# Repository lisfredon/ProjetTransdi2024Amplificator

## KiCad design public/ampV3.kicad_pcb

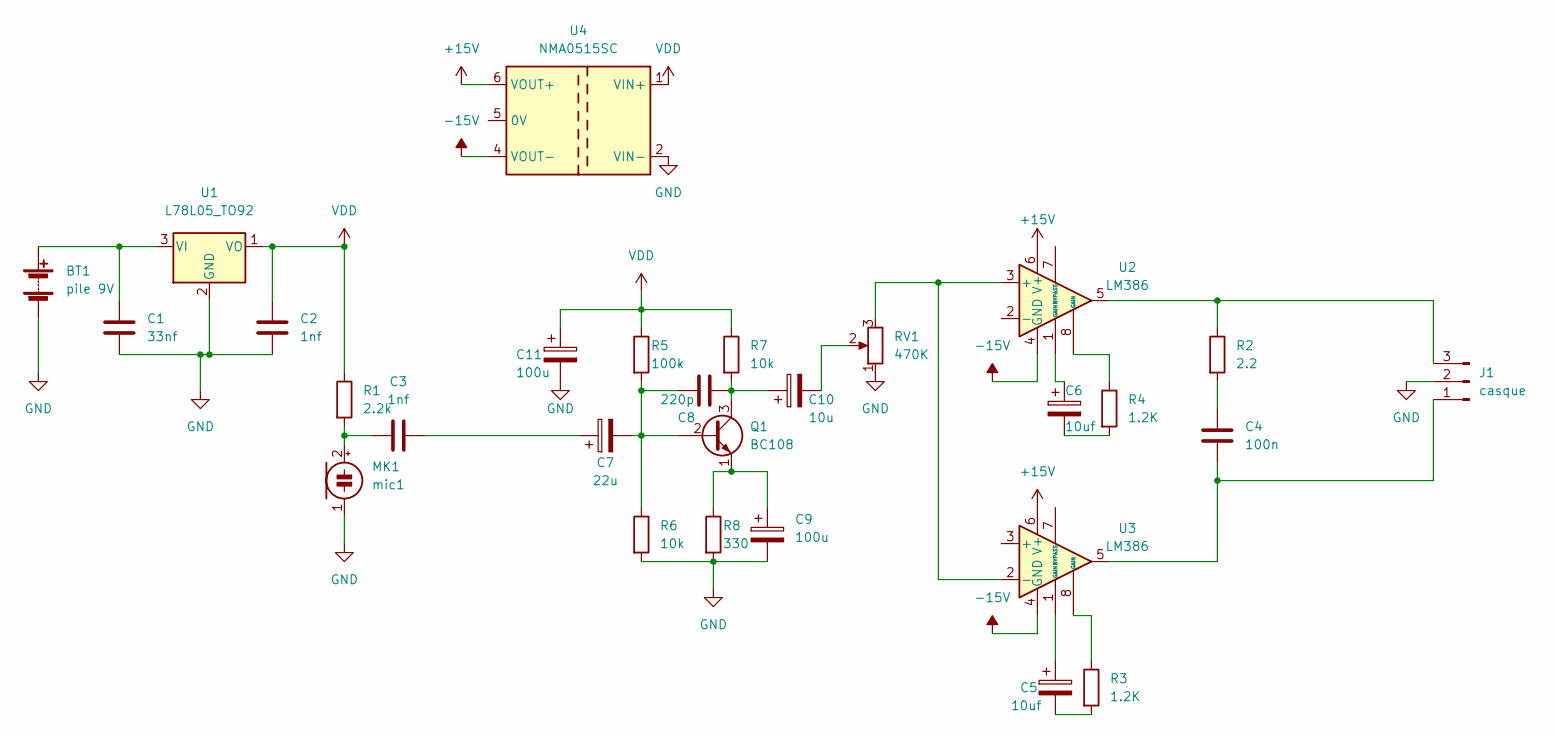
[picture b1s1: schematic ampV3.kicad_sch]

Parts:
BT1: pile 9V; PinHeader_1x02_P2.00mm_Vertical
C1: 33nf; C_Rect_L7.2mm_W3.0mm_P5.00mm_FKS2_FKP2_MKS2_MKP2
C2, C3: 1nf; C_Rect_L7.2mm_W3.0mm_P5.00mm_FKS2_FKP2_MKS2_MKP2
C4: 100n; C_Rect_L7.2mm_W3.0mm_P5.00mm_FKS2_FKP2_MKS2_MKP2
C5, C6: 10uf; CP_Radial_D6.3mm_P2.50mm
C7: 22u; CP_Radial_D6.3mm_P2.50mm
C8: 220p; C_Rect_L7.2mm_W2.5mm_P5.00mm_FKS2_FKP2_MKS2_MKP2
C9, C11: 100u; CP_Radial_D6.3mm_P2.50mm
C10: 10u; CP_Radial_D6.3mm_P2.50mm
J1: casque; PinHeader_1x03_P2.00mm_Vertical
MK1: mic1; PinHeader_1x02_P2.00mm_Vertical
Q1: BC108; TO-18-3
R1: 2.2k; R_Axial_DIN0204_L3.6mm_D1.6mm_P7.62mm_Horizontal
R2: 2.2; R_Axial_DIN0204_L3.6mm_D1.6mm_P7.62mm_Horizontal
R3, R4: 1.2K; R_Axial_DIN0204_L3.6mm_D1.6mm_P7.62mm_Horizontal
R5: 100k; R_Axial_DIN0204_L3.6mm_D1.6mm_P7.62mm_Horizontal
R6, R7: 10k; R_Axial_DIN0204_L3.6mm_D1.6mm_P7.62mm_Horizontal
R8: 330; R_Axial_DIN0204_L3.6mm_D1.6mm_P7.62mm_Horizontal
RV1: 470K; Potentiometer_Piher_PT-10-V05_Vertical
U1: L78L05_TO92; TO-92_Inline_Wide
U2, U3: LM386; DIP-8_W7.62mm_Socket
U4: NMA0515SC; Converter_DCDC_Murata_NMAxxxxSC_THT

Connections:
+15V: U2.6 (V+), U3.6 (V+), U4.6 (VOUT+)
-15V: U2.4 (GND), U3.4 (GND), U4.4 (VOUT-)
GND: BT1.2 (-), C1.2, C2.2, C9.2, C11.2, J1.2, MK1.1 (-), R6.2, R8.2, RV1.1, U1.2 (GND), U4.2 (VIN-)
unnamed: BT1.1 (+), C1.1, U1.3 (VI)
unnamed: C3.2, C7.1
unnamed: C4.1, R2.2
unnamed: C5.1, U3.1 (GAIN)
unnamed: C5.2, R3.2
unnamed: C6.1, U2.1 (GAIN)
unnamed: C6.2, R4.2
unnamed: C10.2, RV1.2
unnamed: C4.2, J1.1, U3.5
unnamed: J1.3, R2.1, U2.5
unnamed: C3.1, MK1.2 (+), R1.2
unnamed: C7.2, C8.1, Q1.2 (B), R5.2, R6.1
unnamed: C8.2, C10.1, Q1.3 (C), R7.2
unnamed: C9.1, Q1.1 (E), R8.1
unnamed: R3.1, U3.8 (GAIN)
unnamed: R4.1, U2.8 (GAIN)
unnamed: RV1.3, U2.3 (+), U3.2 (-)
VDD: C2.1, C11.1, R1.1, R5.1, R7.1, U1.1 (VO), U4.1 (VIN+)

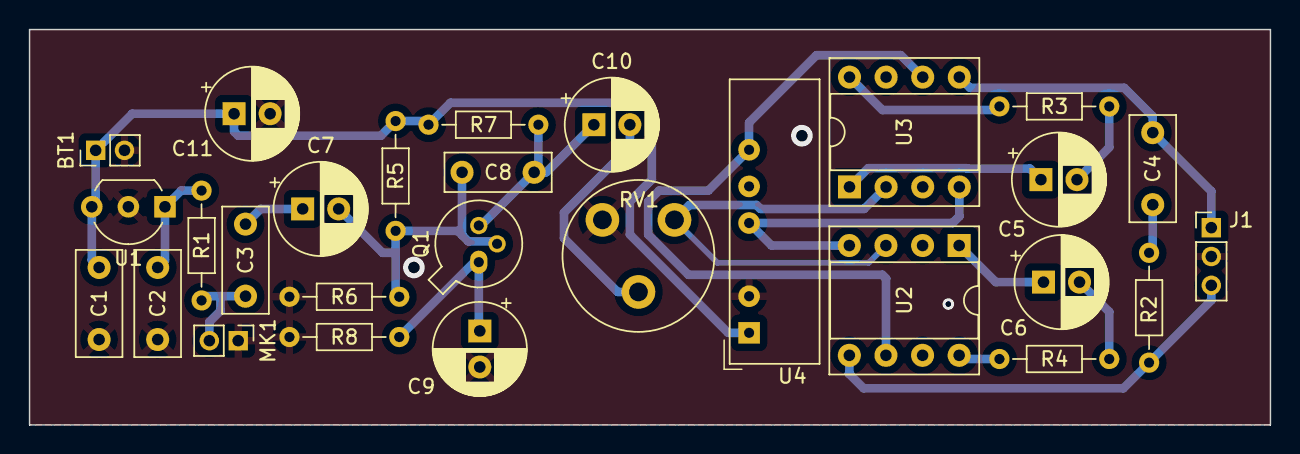
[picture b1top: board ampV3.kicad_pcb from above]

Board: 2 copper layers, 86.1 x 27.4 mm, 28 parts (0 on the bottom side), 21 nets.

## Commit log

2024-05-23 le debut
2024-05-23 nouvelle branche
2024-05-23 début de la structure de la page réalisations
2024-05-23 des ptits trucs
2024-05-23 page pistolet ok
2024-05-23 page boitier ok
2024-05-27 site fini
2024-05-28 ajustement
2024-05-28 retour
2024-05-28 changement
2024-05-28 chore: update build files
2024-05-28 fix gh pages
2024-05-28 c'est good
